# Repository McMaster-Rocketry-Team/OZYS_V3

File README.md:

# OZYS_PCB
OZYS PCB and Schematics

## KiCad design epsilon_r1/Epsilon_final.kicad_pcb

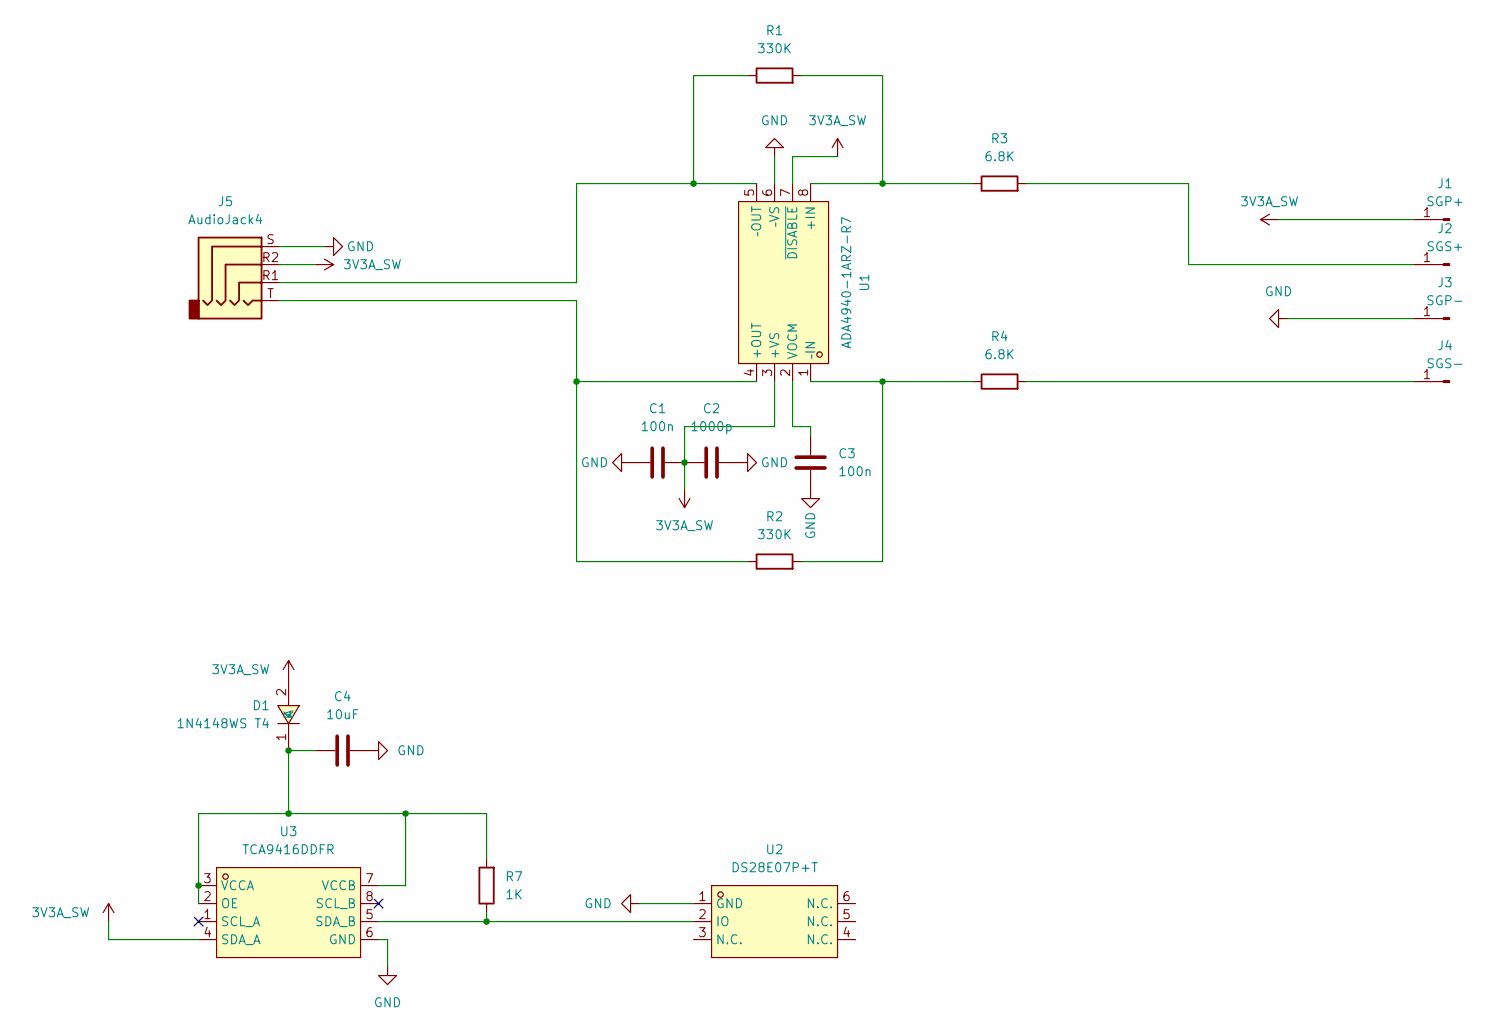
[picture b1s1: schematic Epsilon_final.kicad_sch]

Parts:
C1, C3: 100n; C_0402_1005Metric
C2: 1000p; C_0402_1005Metric
C4: 10uF; C_0402_1005Metric
D1: 1N4148WS T4; SOD-323_L1.8-W1.3-LS2.5-RD; LCSC Part C2128
J1: SGP+; SolderWirePad_1x01_SMD_1x2mm
J2: SGS+; SolderWirePad_1x01_SMD_1x2mm
J3: SGP-; SolderWirePad_1x01_SMD_1x2mm
J4: SGS-; SolderWirePad_1x01_SMD_1x2mm
J5: AudioJack4; AUDIO-TH_PJ-320A-4P-DIP
R1, R2: 330K; R_0603_1608Metric_Pad0.98x0.95mm_HandSolder
R3, R4: 6.8K; R_0603_1608Metric_Pad0.98x0.95mm_HandSolder
R7: 1K; R_0402_1005Metric
U1: ADA4940-1ARZ-R7; LFCSP-16_L3.0-W3.0-P0.50-BL-EP1.3; LCSC Part C730049
U2: DS28E07P+T; TSOC-6_L3.9-W4.3-P1.27-BL; LCSC Part C2063921
U3: TCA9416DDFR; TSOT-23-8_L2.9-W1.6-P0.65-LS2.8-BR; LCSC Part C4364143

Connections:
3V3A_SW: C1.1, C2.2, D1.2 (A), J1.1, J5.R2, U1.3 (+VS), U1.7 (~DISABLE), U3.4 (SDA_A)
GND: C1.2, C2.1, C3.1, C4.2, J3.1, J5.S, U1.6 (–VS), U2.1 (GND), U3.6 (GND)
unnamed: C4.1, D1.1 (K), R7.2, U3.2 (OE), U3.3 (VCCA), U3.7 (VCCB)
unnamed: J2.1, R3.2
unnamed: J4.1, R4.2
unnamed: R1.2, R3.1, U1.8 (+IN)
unnamed: J5.T, R2.1, U1.4 (+OUT)
unnamed: C3.2, U1.2 (VOCM)
unnamed: R2.2, R4.1, U1.1 (–IN)
unnamed: J5.R1, R1.1, U1.5 (–OUT)
unnamed: R7.1, U2.2 (IO), U3.5 (SDA_B)

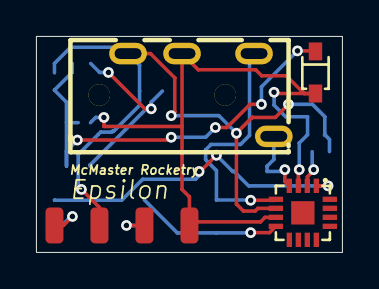
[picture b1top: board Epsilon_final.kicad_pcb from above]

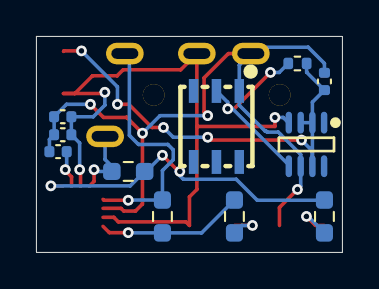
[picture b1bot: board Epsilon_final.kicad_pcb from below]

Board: 2 copper layers, 17.0 x 12.0 mm, 18 parts (11 on the bottom side), 11 nets.

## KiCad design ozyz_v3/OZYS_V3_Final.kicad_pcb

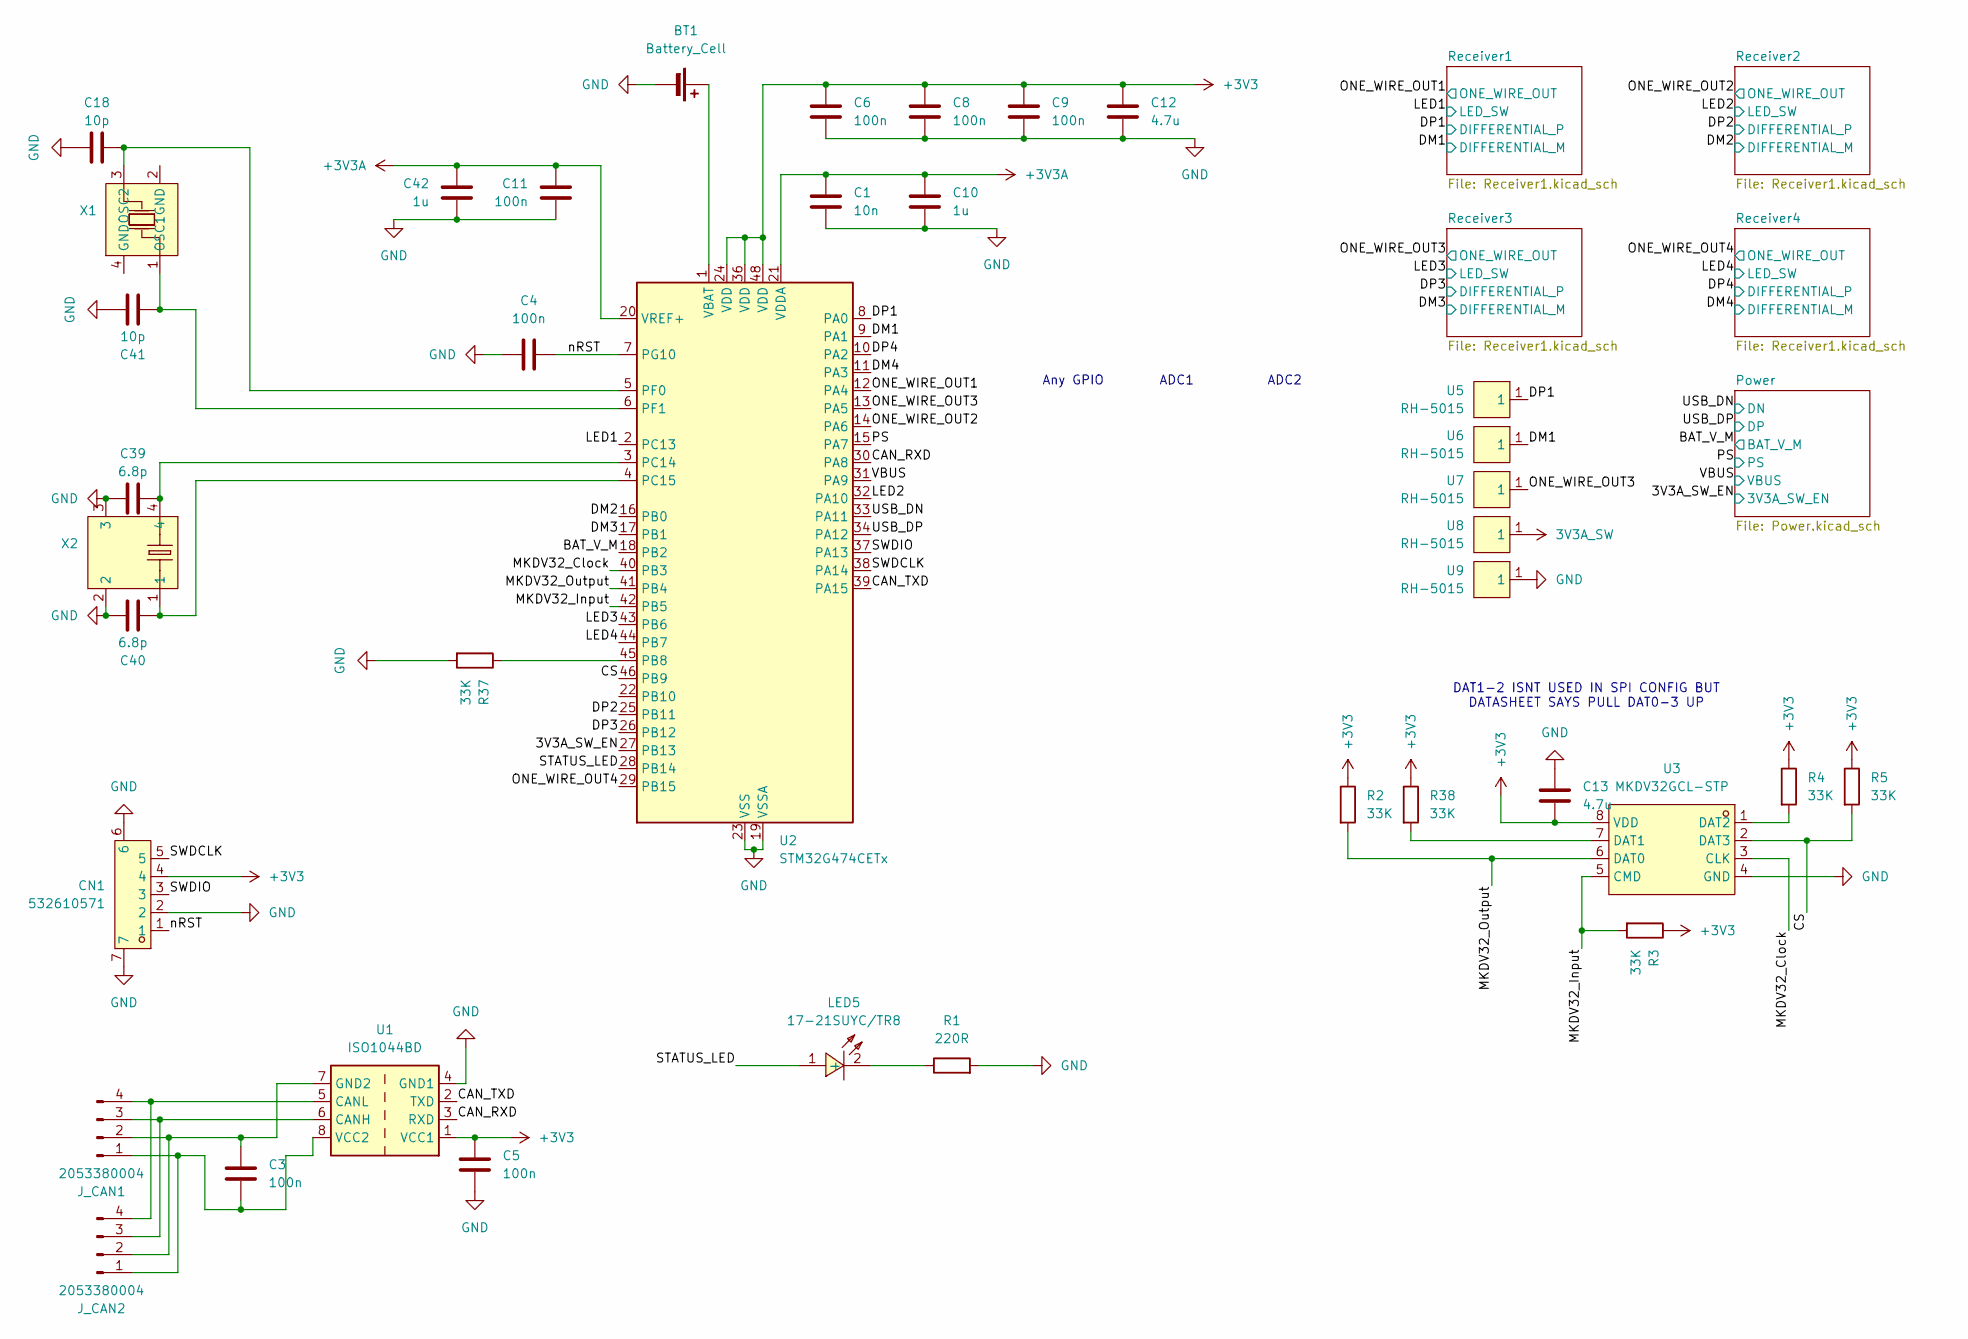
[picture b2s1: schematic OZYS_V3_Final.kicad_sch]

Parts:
BT1: Battery_Cell; SEIKO_ML414H_IV01E
C1: 10n; C_0402_1005Metric
C3, C4, C5, C6, C8, C9, C11: 100n; C_0402_1005Metric
C10, C42: 1u; C_0402_1005Metric
C12, C13: 4.7u; C_0402_1005Metric
C18, C41: 10p; C_0603_1608Metric_Pad1.08x0.95mm_HandSolder
C39, C40: 6.8p; C_0603_1608Metric_Pad1.08x0.95mm_HandSolder
CN1: 532610571; CONN-SMD_5P-P1.25_532610571-2; LCSC Part C392176
J_CAN1, J_CAN2: 2053380004; CONN_2053380000-SD_04_MOL
LED5: 17-21SUYC/TR8; LED0805-R-RD; LCSC Part C2296
R1: 220R; R_0402_1005Metric
R2, R3, R4, R5, R37, R38: 33K; R_0402_1005Metric
U1: ISO1044BD; SOIC-8_3.9x4.9mm_P1.27mm
U2: STM32G474CETx; LQFP-48_7x7mm_P0.5mm
U3: MKDV32GCL-STP; LGA-8_L6.0-W8.0-P1.27-TL; LCSC Part C7500179
U5, U6, U7, U8, U9: RH-5015; SMD_RH-5015; LCSC Part C5199798
X1: X322516MLB4SI; OSC-SMD_4P-L3.2-W2.5-BL; LCSC Part C13738
X2: MC-306 32.768kHz 6.0pF 20ppm; MC-306_4P-L8.0-W3.2-P5.5-BL; LCSC Part C83979

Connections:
3V3A_SW: U8.1; also elsewhere on the board
+3V3: C5.2, C6.1, C8.1, C9.1, C12.1, C13.2, CN1.4, R2.1, R3.1, R4.1, R5.1, R38.1, U1.1 (VCC1), U2.24 (VDD), U2.36 (VDD), U2.48 (VDD), U3.8 (VDD); also elsewhere on the board
+3V3A: C1.1, C10.2, C11.1, C42.2, U2.20 (VREF+), U2.21 (VDDA); also elsewhere on the board
/3V3A_SW_EN: U2.27 (PB13); also elsewhere on the board
/BAT_V_M: U2.18 (PB2); also elsewhere on the board
/CAN_RXD: U1.3 (RXD), U2.30 (PA8)
/CAN_TXD: U1.2 (TXD), U2.39 (PA15)
/CS: R5.2, U2.46 (PB9), U3.2 (DAT3)
/DM1: U2.9 (PA1), U6.1; also elsewhere on the board
/DM2: U2.16 (PB0); also elsewhere on the board
/DM3: U2.17 (PB1); also elsewhere on the board
/DM4: U2.11 (PA3); also elsewhere on the board
/DP1: U2.8 (PA0), U5.1; also elsewhere on the board
/DP2: U2.25 (PB11); also elsewhere on the board
/DP3: U2.26 (PB12); also elsewhere on the board
/DP4: U2.10 (PA2); also elsewhere on the board
/LED1: U2.2 (PC13); also elsewhere on the board
/LED2: U2.32 (PA10); also elsewhere on the board
/LED3: U2.43 (PB6); also elsewhere on the board
/LED4: U2.44 (PB7); also elsewhere on the board
/MKDV32_Clock: U2.40 (PB3), U3.3 (CLK)
/MKDV32_Input: R3.2, U2.42 (PB5), U3.5 (CMD)
/MKDV32_Output: R2.2, U2.41 (PB4), U3.6 (DAT0)
/ONE_WIRE_OUT1: U2.12 (PA4); also elsewhere on the board
/ONE_WIRE_OUT2: U2.14 (PA6); also elsewhere on the board
/ONE_WIRE_OUT3: U2.13 (PA5), U7.1; also elsewhere on the board
/ONE_WIRE_OUT4: U2.29 (PB15); also elsewhere on the board
/PS: U2.15 (PA7); also elsewhere on the board
/STATUS_LED: LED5.1 (+), U2.28 (PB14)
/SWDCLK: CN1.5, U2.38 (PA14)
/SWDIO: CN1.3, U2.37 (PA13)
/USB_DN: U2.33 (PA11); also elsewhere on the board
/USB_DP: U2.34 (PA12); also elsewhere on the board
/VBUS: U2.31 (PA9); also elsewhere on the board
/nRST: C4.2, CN1.1, U2.7 (PG10)
GND: BT1.2 (-), C1.2, C4.1, C5.1, C6.2, C8.2, C9.2, C10.1, C11.2, C12.2, C13.1, C18.1, C39.1, C40.2, C41.1, C42.1, CN1.2, CN1.6, CN1.7, R1.2, R37.2, U1.4 (GND1), U2.19 (VSSA), U2.23 (VSS), U2.35 (VSS), U2.47 (VSS), U3.4 (GND), U9.1, X2.2, X2.3; also elsewhere on the board
unnamed: BT1.1 (+), U2.1 (VBAT)
unnamed: C3.2, J_CAN1.1, J_CAN2.1, U1.8 (VCC2)
unnamed: C3.1, J_CAN1.2, J_CAN2.2, U1.7 (GND2)
unnamed: J_CAN1.3, J_CAN2.3, U1.6 (CANH)
unnamed: J_CAN1.4, J_CAN2.4, U1.5 (CANL)
unnamed: LED5.2 (-), R1.1
unnamed: R37.1, U2.45 (PB8)
unnamed: C39.2, U2.3 (PC14), X2.4
unnamed: C40.1, U2.4 (PC15), X2.1
unnamed: C18.2, U2.5 (PF0), X1.3 (OSC2)
unnamed: C41.2, U2.6 (PF1), X1.1 (OSC1)
unnamed: R38.2, U3.7 (DAT1)
unnamed: R4.2, U3.1 (DAT2)

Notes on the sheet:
ADC1
ADC2
DAT1-2 ISNT USED IN SPI CONFIG BUT DATASHEET SAYS PULL DAT0-3 UP
Any GPIO

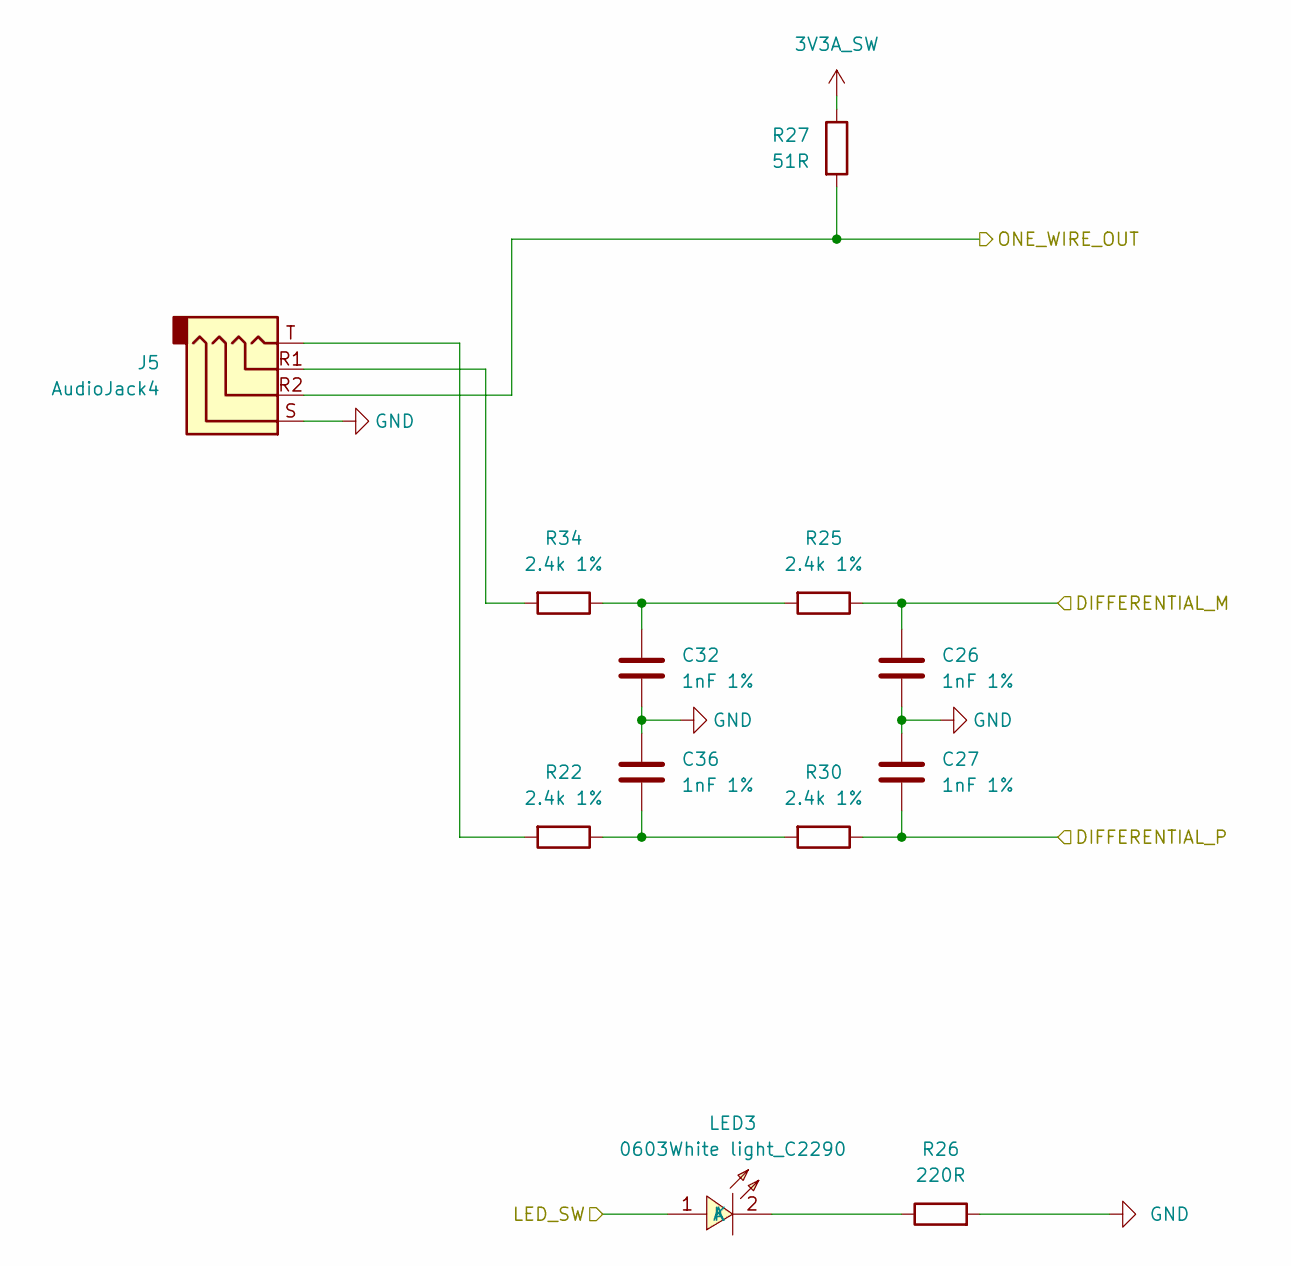
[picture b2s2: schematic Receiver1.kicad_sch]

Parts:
C26, C27, C32, C36: 1nF 1%; C_0603_1608Metric_Pad1.08x0.95mm_HandSolder
J5: AudioJack4; AUDIO-TH_PJ-320A-4P-DIP
LED3: 0603White light_C2290; LED0603-R-RD_WHITE; LCSC Part C2290
R22, R25, R30, R34: 2.4k 1%; C_0603_1608Metric_Pad1.08x0.95mm_HandSolder
R26: 220R; R_0402_1005Metric
R27: 51R; R_0402_1005Metric

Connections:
3V3A_SW: R27.1; also elsewhere on the board
/DM3: C26.1, R25.1; also elsewhere on the board
/DP3: C27.2, R30.1; also elsewhere on the board
/LED3: LED3.1 (A); also elsewhere on the board
/ONE_WIRE_OUT3: J5.R2, R27.2; also elsewhere on the board
GND: C26.2, C27.1, C32.2, C36.1, J5.S, R26.2; also elsewhere on the board
unnamed: C32.1, R25.2, R34.1
unnamed: C36.2, R22.1, R30.2
unnamed: J5.R1, R34.2
unnamed: J5.T, R22.2
unnamed: LED3.2 (K), R26.1

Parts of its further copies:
C2, C7, C22, C24, C28, C29, C30, C31, C33, C34, C35, C37: 1nF 1%; C_0603_1608Metric_Pad1.08x0.95mm_HandSolder
J3, J4, J6: AudioJack4; AUDIO-TH_PJ-320A-4P-DIP
LED1, LED2, LED4: 0603White light_C2290; LED0603-R-RD_WHITE; LCSC Part C2290
R13, R14, R19, R20, R21, R23, R24, R28, R29, R31, R35, R36: 2.4k 1%; C_0603_1608Metric_Pad1.08x0.95mm_HandSolder
R15, R17, R32: 220R; R_0402_1005Metric
R16, R18, R33: 51R; R_0402_1005Metric

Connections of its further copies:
3V3A_SW: R16.1, R18.1, R33.1; also elsewhere on the board
/DM1: C2.1, R13.1; also elsewhere on the board
/DM2: C22.1, R21.1; also elsewhere on the board
/DM4: C28.1, R31.1; also elsewhere on the board
/DP1: C7.2, R14.1; also elsewhere on the board
/DP2: C24.2, R24.1; also elsewhere on the board
/DP4: C29.2, R36.1; also elsewhere on the board
/LED1: LED2.1 (A); also elsewhere on the board
/LED2: LED1.1 (A); also elsewhere on the board
/LED4: LED4.1 (A); also elsewhere on the board
/ONE_WIRE_OUT1: J3.R2, R16.2; also elsewhere on the board
/ONE_WIRE_OUT2: J4.R2, R18.2; also elsewhere on the board
/ONE_WIRE_OUT4: J6.R2, R33.2; also elsewhere on the board
GND: C2.2, C7.1, C22.2, C24.1, C28.2, C29.1, C30.2, C31.2, C33.2, C34.1, C35.1, C37.1, J3.S, J4.S, J6.S, R15.2, R17.2, R32.2; also elsewhere on the board
unnamed: C30.1, R13.2, R28.1
unnamed: C31.1, R21.2, R29.1
unnamed: C33.1, R31.2, R35.1
unnamed: C34.2, R14.2, R19.1
unnamed: C35.2, R20.1, R24.2
unnamed: C37.2, R23.1, R36.2
unnamed: J3.R1, R28.2
unnamed: J3.T, R19.2
unnamed: J4.R1, R29.2
unnamed: J4.T, R20.2
unnamed: J6.R1, R35.2
unnamed: J6.T, R23.2
unnamed: LED1.2 (K), R17.1
unnamed: LED2.2 (K), R15.1
unnamed: LED4.2 (K), R32.1

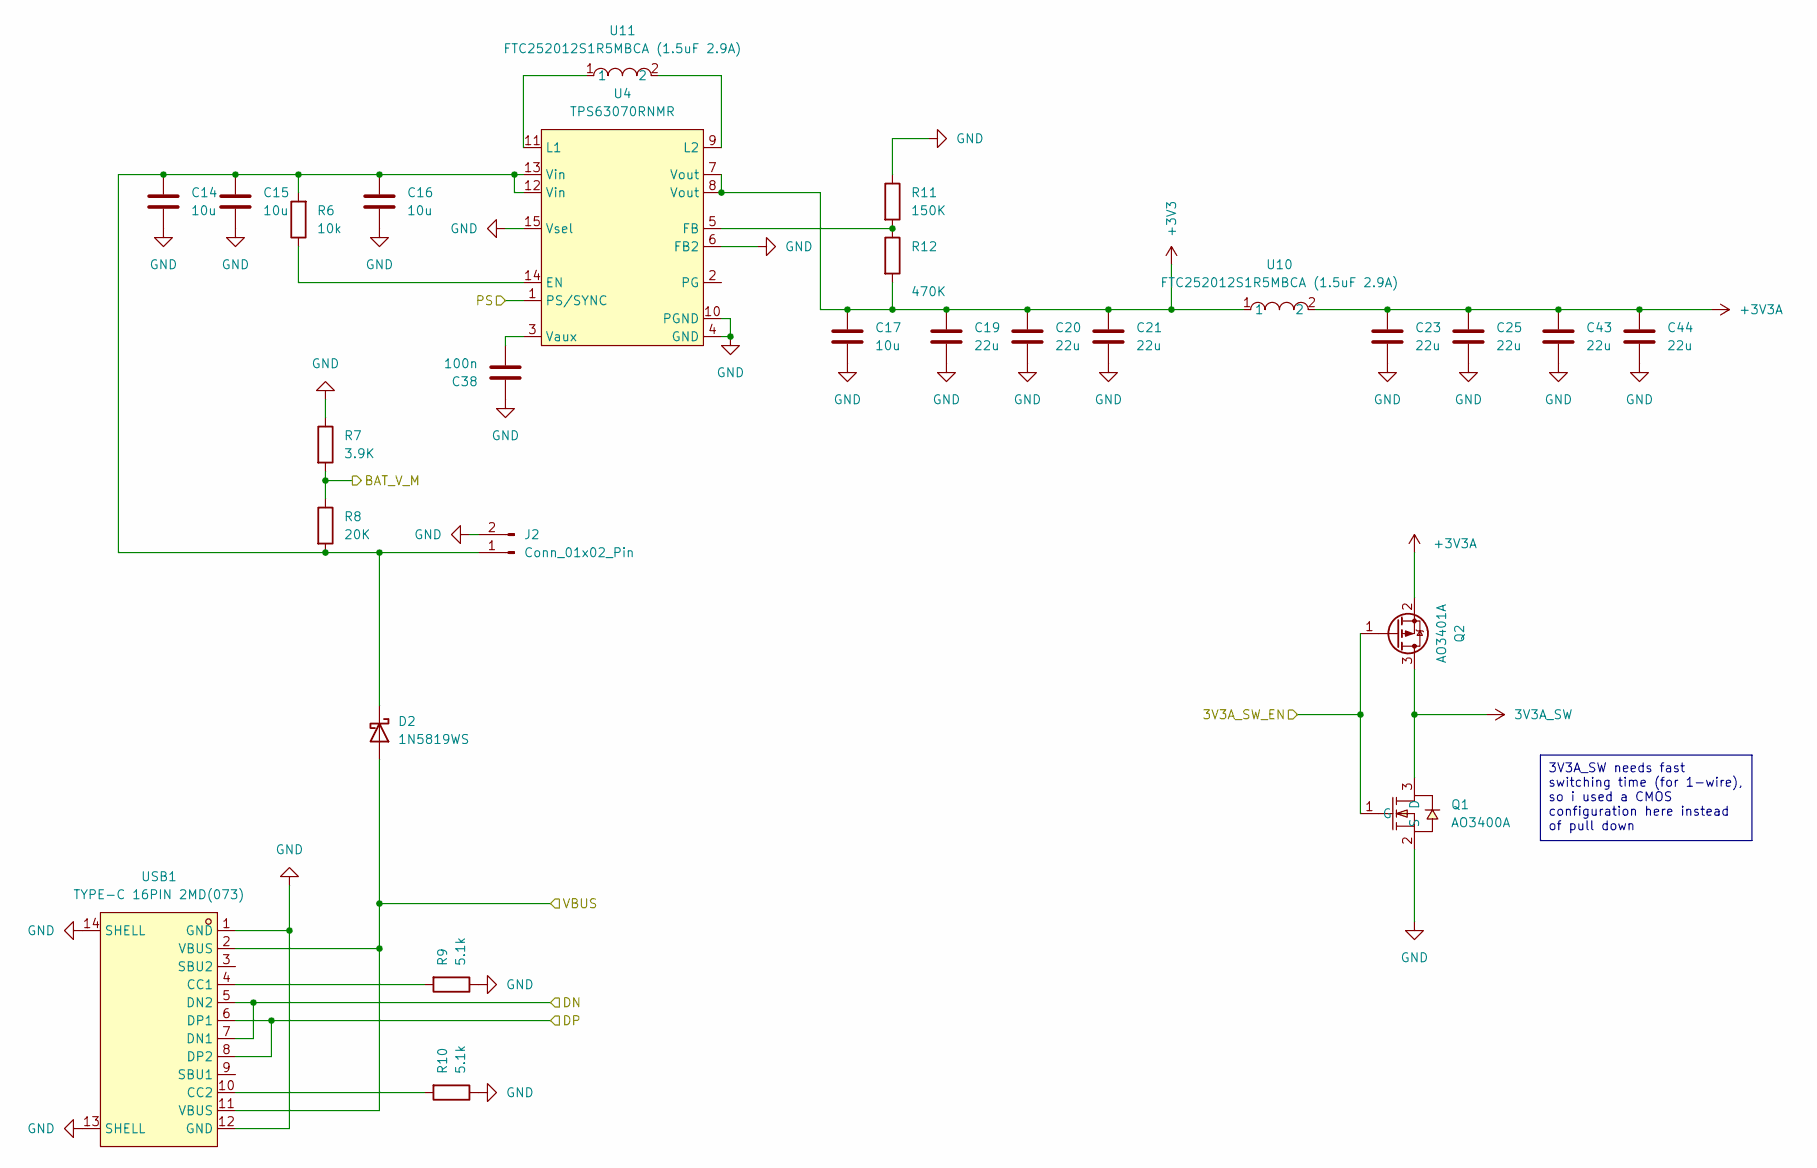
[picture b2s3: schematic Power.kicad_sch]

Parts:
C14, C15, C16, C17: 10u; C_0603_1608Metric
C19, C20, C21, C23, C25, C43, C44: 22u; C_0603_1608Metric
C38: 100n; C_0402_1005Metric
D2: 1N5819WS; D_SOD-323
J2: Conn_01x02_Pin; 1054301102
Q1: AO3400A; SOT-23-3_L2.9-W1.3-P1.90-LS2.4-BR; LCSC Part C20917
Q2: AO3401A; SOT-23
R6: 10k; R_0402_1005Metric
R7: 3.9K; R_0402_1005Metric
R8: 20K; R_0402_1005Metric
R9, R10: 5.1k; R_0402_1005Metric
R11: 150K; R_0402_1005Metric
R12: 470K; R_0402_1005Metric
U4: TPS63070RNMR; VQFN-HR-15_L3.0-W2.5-P0.50-BL_TPS63070RNMR; LCSC Part C109322
U10, U11: FTC252012S1R5MBCA (1.5uF 2.9A); IND-SMD_L2.5-W2.0_MEKK2520TR47M; LCSC Part C5832371
USB1: TYPE-C 16PIN 2MD(073); USB-C-SMD_TYPE-C-6PIN-2MD-073; LCSC Part C2765186

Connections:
3V3A_SW: Q1.3 (D), Q2.3 (D); also elsewhere on the board
+3V3: C17.2, C19.2, C20.2, C21.2, R12.2, U4.7 (Vout), U4.8 (Vout), U10.1; also elsewhere on the board
+3V3A: C23.2, C25.2, C43.2, C44.2, Q2.2 (S), U10.2; also elsewhere on the board
/3V3A_SW_EN: Q1.1 (G), Q2.1 (G); also elsewhere on the board
/BAT_V_M: R7.2, R8.1; also elsewhere on the board
/PS: U4.1 (PS/SYNC); also elsewhere on the board
/USB_DN: USB1.5 (DN2), USB1.7 (DN1); also elsewhere on the board
/USB_DP: USB1.6 (DP1), USB1.8 (DP2); also elsewhere on the board
/VBUS: D2.2 (A), USB1.2 (VBUS), USB1.11 (VBUS); also elsewhere on the board
GND: C14.1, C15.1, C16.1, C17.1, C19.1, C20.1, C21.1, C23.1, C25.1, C38.2, C43.1, C44.1, J2.2, Q1.2 (S), R7.1, R9.1, R10.1, R11.1, U4.4 (GND), U4.6 (FB2), U4.10 (PGND), U4.15 (Vsel), USB1.1 (GND), USB1.12 (GND), USB1.13 (SHELL), USB1.14 (SHELL); also elsewhere on the board
unnamed: C14.2, C15.2, C16.2, D2.1 (K), J2.1, R6.2, R8.2, U4.12 (Vin), U4.13 (Vin)
unnamed: R6.1, U4.14 (EN)
unnamed: R11.2, R12.1, U4.5 (FB)
unnamed: U4.11 (L1), U11.1
unnamed: U4.9 (L2), U11.2
unnamed: C38.1, U4.3 (Vaux)
unnamed: R9.2, USB1.4 (CC1)
unnamed: R10.2, USB1.10 (CC2)

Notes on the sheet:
3V3A_SW needs fast switching time (for 1-wire), so i used a CMOS configuration here instead of pull down

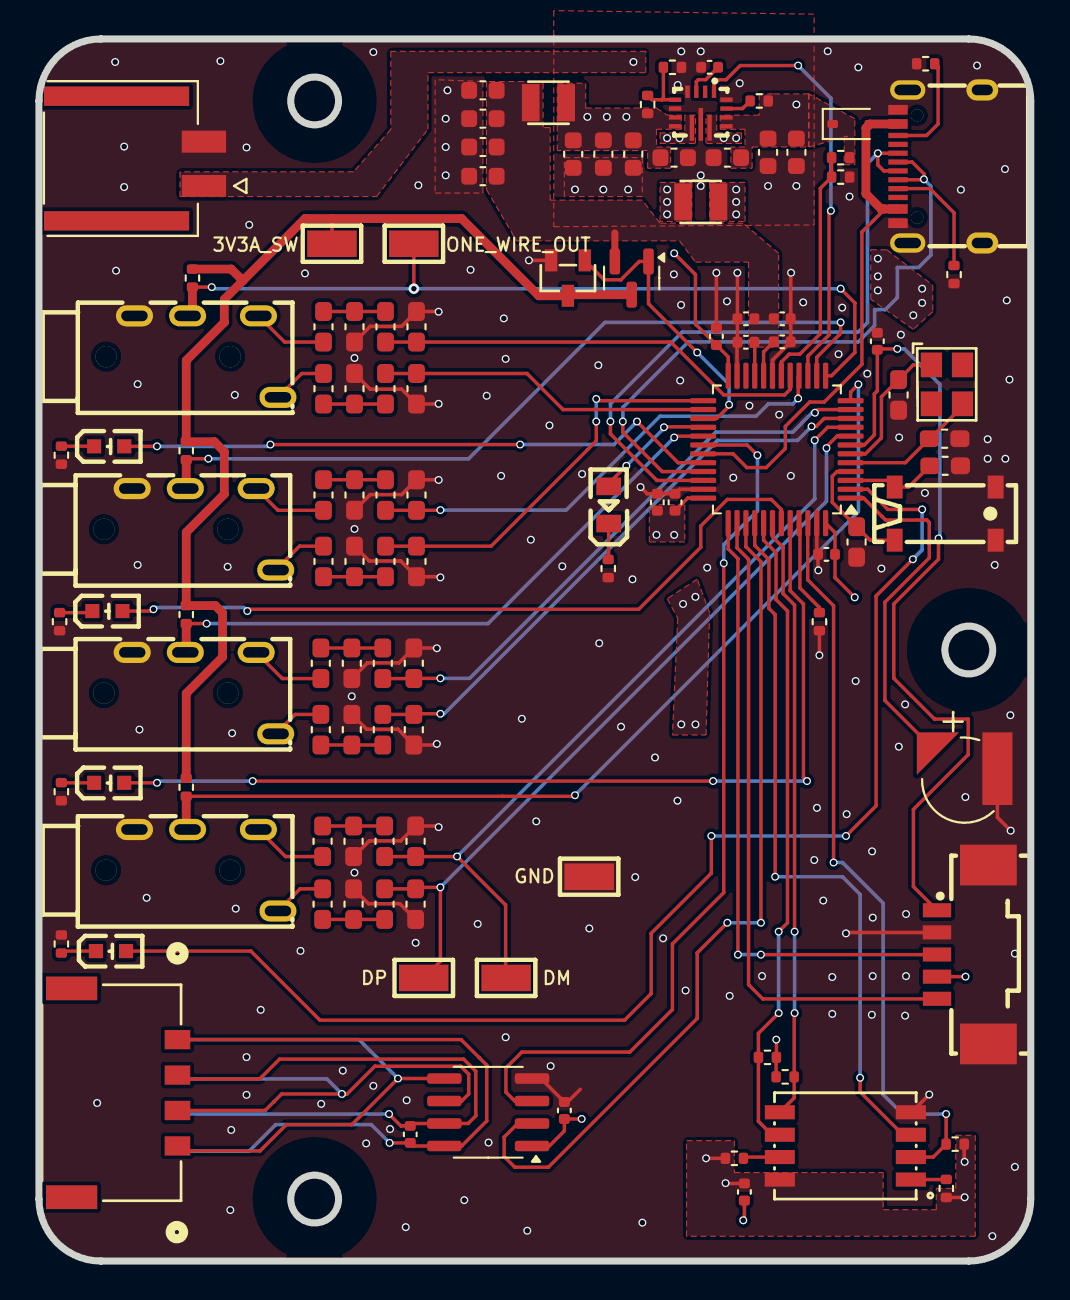
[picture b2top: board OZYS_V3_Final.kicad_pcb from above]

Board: 4 copper layers, 56.0 x 69.0 mm, 113 parts (1 on the bottom side), 77 nets.

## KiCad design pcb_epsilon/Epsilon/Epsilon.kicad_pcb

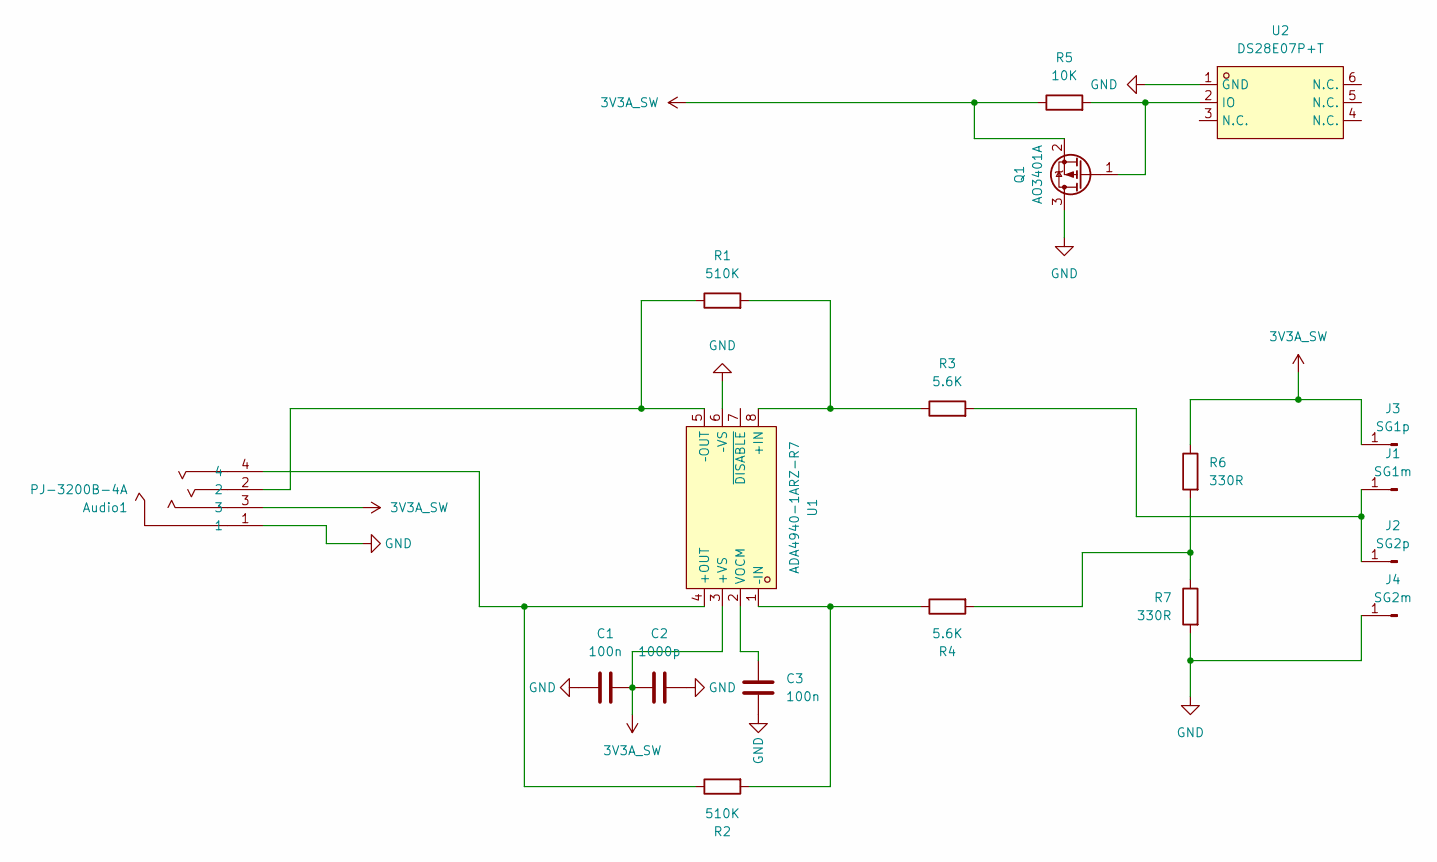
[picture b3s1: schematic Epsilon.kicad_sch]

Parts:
Audio1: PJ-3200B-4A; AUDIO-TH_PJ-3200B-4A; LCSC Part C136687
C1, C3: 100n; C_0402_1005Metric
C2: 1000p; C_0402_1005Metric
J1: SG1m; SolderWirePad_1x01_SMD_1x2mm
J2: SG2p; SolderWirePad_1x01_SMD_1x2mm
J3: SG1p; SolderWirePad_1x01_SMD_1x2mm
J4: SG2m; SolderWirePad_1x01_SMD_1x2mm
Q1: AO3401A; SOT-23
R1, R2: 510K; R_0603_1608Metric_Pad0.98x0.95mm_HandSolder
R3, R4: 5.6K; R_0603_1608Metric_Pad0.98x0.95mm_HandSolder
R5: 10K; R_0402_1005Metric_Pad0.72x0.64mm_HandSolder
R6, R7: 330R; R_0402_1005Metric_Pad0.72x0.64mm_HandSolder
U1: ADA4940-1ARZ-R7; SOIC-8_L4.9-W3.9-P1.27-LS6.0-BL; LCSC Part C730049
U2: DS28E07P+T; TSOC-6_L3.9-W4.3-P1.27-BL; LCSC Part C2063921

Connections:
3V3A_SW: Audio1.3, C1.1, C2.2, J3.1, Q1.2 (S), R5.1, R6.1, U1.3 (+VS)
GND: Audio1.1, C1.2, C2.1, C3.1, J4.1, Q1.3 (D), R7.2, U1.6 (–VS), U2.1 (GND)
unnamed: J1.1, J2.1, R3.2
unnamed: Q1.1 (G), R5.2, U2.2 (IO)
unnamed: R4.2, R6.2, R7.1
unnamed: R1.2, R3.1, U1.8 (+IN)
unnamed: Audio1.4, R2.1, U1.4 (+OUT)
unnamed: C3.2, U1.2 (VOCM)
unnamed: R2.2, R4.1, U1.1 (–IN)
unnamed: Audio1.2, R1.1, U1.5 (–OUT)

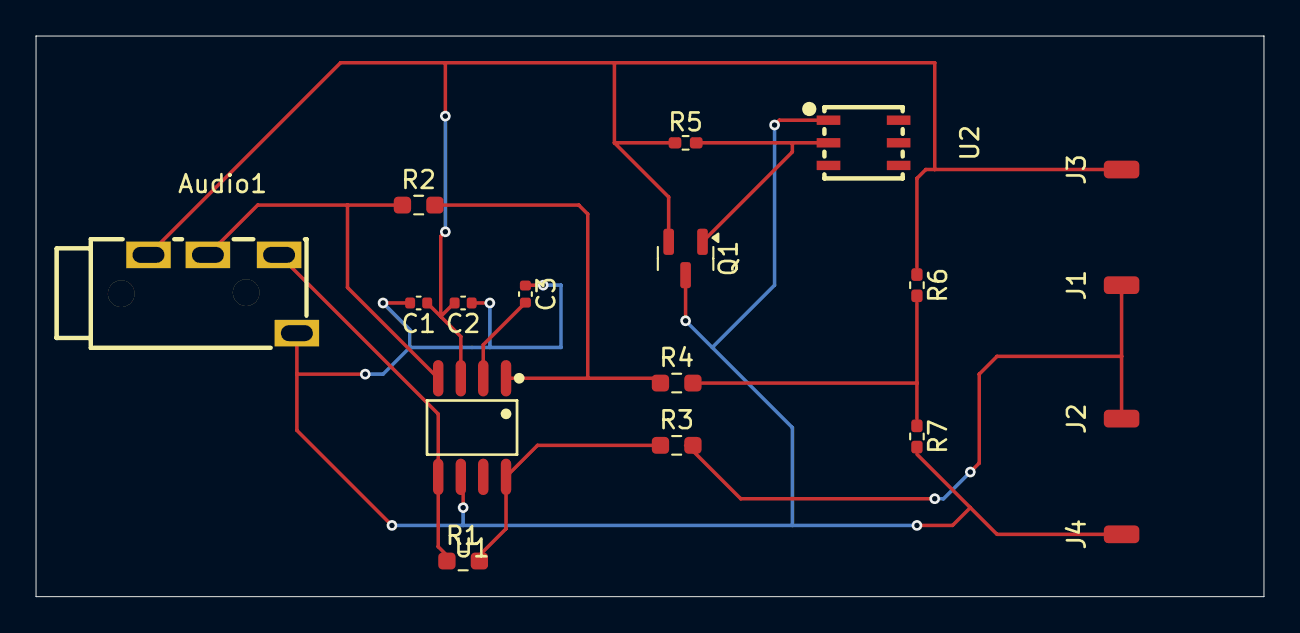
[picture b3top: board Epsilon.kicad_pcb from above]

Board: 2 copper layers, 69.0 x 31.5 mm, 18 parts (0 on the bottom side), 10 nets.

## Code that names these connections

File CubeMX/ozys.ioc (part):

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Mcu.Name=STM32G474C(B-C-E)Tx
Mcu.Package=LQFP48
Mcu.UserName=STM32G474CETx
PA0.Mode=IN1-Differential
PA0.Signal=ADC1_IN1
PA1.Mode=IN1-Differential
PA1.Signal=ADC1_IN2
PA11.Mode=Device
PA11.Signal=USB_DM
PA12.Mode=Device
PA12.Signal=USB_DP
PA13.Mode=Serial_Wire
PA13.Signal=SYS_JTMS-SWDIO
PA14.Mode=Serial_Wire
PA14.Signal=SYS_JTCK-SWCLK
PA15.Mode=FDCAN_Activate
PA15.Signal=FDCAN3_TX
PA2.Mode=IN3-Differential
PA2.Signal=ADC1_IN3
PA3.Mode=IN3-Differential
PA3.Signal=ADC1_IN4
PA4.Mode=IN17-Single-Ended
PA4.Signal=ADC2_IN17
PA5.Mode=IN13-Single-Ended
PA5.Signal=ADC2_IN13
PA6.Mode=IN3-Single-Ended
PA6.Signal=ADC2_IN3
PA8.Mode=FDCAN_Activate
PA8.Signal=FDCAN3_RX
PB0.Mode=IN14-Differential
PB0.Signal=ADC1_IN15
PB1.Mode=IN11-Differential
PB1.Signal=ADC1_IN12
PB11.Mode=IN14-Differential
PB11.Signal=ADC1_IN14
PB12.Mode=IN11-Differential
PB12.Signal=ADC1_IN11
PB15.Mode=IN15-Single-Ended
PB15.Signal=ADC2_IN15
PB2.Mode=IN12-Single-Ended
PB2.Signal=ADC2_IN12
PB3.Mode=Full_Duplex_Master
PB3.Signal=SPI1_SCK
PB4.Mode=Full_Duplex_Master
PB4.Signal=SPI1_MISO
PB5.Mode=Full_Duplex_Master
PB5.Signal=SPI1_MOSI
PC14-OSC32_IN.Mode=LSE-External-Oscillator
PC14-OSC32_IN.Signal=RCC_OSC32_IN
PC15-OSC32_OUT.Mode=LSE-External-Oscillator
PC15-OSC32_OUT.Signal=RCC_OSC32_OUT
PF0-OSC_IN.Mode=HSE-External-Oscillator
PF0-OSC_IN.Signal=RCC_OSC_IN
PF1-OSC_OUT.Mode=HSE-External-Oscillator
PF1-OSC_OUT.Signal=RCC_OSC_OUT
RCC.HSE_VALUE=16000000
RCC.SYSCLKFreq_VALUE=150000000
RCC.SYSCLKSource=RCC_SYSCLKSOURCE_PLLCLK
board=custom

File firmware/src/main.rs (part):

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    Peri,
    adc::{Adc, AdcChannel, SampleTime},
    crc::{Config as CrcConfig, Crc, InputReverseConfig, PolySize},
    peripherals::{ADC1, DMA1_CH1, PA0, PA2, PA10, PB6, PB7, PB11, PB12, PB14, PC13},
};
use embassy_stm32::{
    gpio::{Level, Output, Speed},
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
use embassy_embedded_hal::shared_bus::asynch::spi::SpiDevice;
use embassy_stm32::spi::{Config as SpiConfig, Spi};
use embassy_stm32::{peripherals::PB3, time::Hertz};
use embedded_sdmmc::asynchronous::{Block, BlockDevice as _, BlockIdx, SdCard};
use firmware_common_new::can_bus::{
    custom_status::ozys_custom_status::OzysCustomStatus,
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    // Peripherals

    // TOP TO BOTTOM ORDERING OF LEDS
    // led 2: PA10
    // led 3: PB6
    // led 4: PB7
    // led 1: PC13
    // status led: PB14

    let ps = Output::new(p.PA7, Level::Low, Speed::Low); // PS pin, low: force pwm 
    mem::forget(ps);

    let (can_sender, can_receiver) = start_can_bus_tasks(&spawner, p.FDCAN3, p.PA8, p.PA15).await;
    spawner.must_spawn(watchdog_task(p.IWDG));
    spawner.must_spawn(node_status_task(can_sender));
    spawner.must_spawn(status_led_task(p.PB14));
    spawner.must_spawn(can_vl_status_check(
        can_receiver,
        flight_stage_watch.sender(),
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    spawner.must_spawn(adc_test_task(
        adc,
        p.DMA1_CH1,
        p.PA0,
        p.PA2,
        p.PB11,
        p.PB12,
        read_buffer,
        adc_samples_channel.publisher().unwrap(),
        converted_samples,
        flight_stage_watch.receiver().unwrap(),
        p.PA10,
        p.PB6,
        p.PB7,
        p.PC13,
    ));

    // sd
    let cs = Output::new(p.PB9, Level::High, Speed::High); // needed to configure as spi mode on peripheral  
    let mut spi_config = SpiConfig::default();
    spi_config.frequency = Hertz(5_000_000);
    let spi1: Spi<'static, embassy_stm32::mode::Async> = Spi::new(
        p.SPI1, p.PB3, p.PB5, p.PB4, p.DMA1_CH2, p.DMA1_CH3, spi_config,
    );
    let spi1 = singleton!(:Mutex<NoopRawMutex, Spi<'static, embassy_stm32::mode::Async>> = Mutex::new(spi1)).unwrap();
    let crc_config =
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async fn adc_test_task(
    mut adc_peripheral: Adc<'static, ADC1>,
    mut dma_chanel: Peri<'static, DMA1_CH1>,
    mut adc_pin_1: Peri<'static, PA0>,
    mut adc_pin_2: Peri<'static, PA2>,
    mut adc_pin_3: Peri<'static, PB11>,
    mut adc_pin_4: Peri<'static, PB12>,
    read_buffer: &'static mut [u16; 5],
    publisher: Publisher<'static, NoopRawMutex, [f32; 4], 620, 2, 1>,
    converted_samples: &'static mut [f32; 4],
    mut state_watch_rx: embassy_sync::watch::Receiver<'static, NoopRawMutex, FlightStage, 2>,
    led_2_pin: Peri<'static, PA10>,
    led_3_pin: Peri<'static, PB6>,
    led_4_pin: Peri<'static, PB7>,
    led_1_pin: Peri<'static, PC13>,
) {
    let mut vrefint_channel = adc_peripheral.enable_vrefint().degrade_adc();
    adc_peripheral.set_sample_time(SampleTime::CYCLES247_5);
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    adc_peripheral.set_differential(&mut adc_pin_2, true);
    adc_peripheral.set_differential(&mut adc_pin_3, true);
    adc_peripheral.set_differential(&mut adc_pin_4, true);
    let mut pa0 = adc_pin_1.degrade_adc();
    let mut pa2 = adc_pin_2.degrade_adc();
    let mut pb11 = adc_pin_3.degrade_adc();
    let mut pb12 = adc_pin_4.degrade_adc();
    let VREFINT_CAL = 0x1FFF75AA as *mut u16;
    let vref_cal = unsafe { ptr::read_volatile(VREFINT_CAL) as f32 };
    info!("VREFINT_CAL: {}", vref_cal);
    let mut ticker = Ticker::every(Duration::from_hz(22_000));
    let mut _led2 = Output::new(led_2_pin, Level::Low, Speed::Low); // good 
    let mut _led3 = Output::new(led_3_pin, Level::Low, Speed::Low); // good
    let mut _led4 = Output::new(led_4_pin, Level::Low, Speed::Low); // good 
    let mut _led1 = Output::new(led_1_pin, Level::Low, Speed::Low); // good

    let mut last_state = state_watch_rx.get().await;
    loop {
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                        | FlightStage::DrogueChute
                        | FlightStage::MainChute
                ) {
                    // led 2: PA10
                    // led 3: PB6
                    // led 4: PB7
                    // led 1: PC13
                    // status led: PB14
                    _led2.set_high();
                    _led3.set_high();
                    _led4.set_high();
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                            dma_chanel.reborrow(),
                            [
                                (&mut vrefint_channel, SampleTime::CYCLES12_5),
                                (&mut pa0, SampleTime::CYCLES12_5),
                                (&mut pa2, SampleTime::CYCLES12_5),
                                (&mut pb11, SampleTime::CYCLES12_5),
                                (&mut pb12, SampleTime::CYCLES12_5),
                            ]
                            .into_iter(),
                            read_buffer,
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}

#[embassy_executor::task]
async fn status_led_task(yellow_led: Peri<'static, PB14>) {
    let mut yellow_led = Output::new(yellow_led, Level::High, Speed::Low);
    let mut ticker = Ticker::every(Duration::from_millis(1000));
    loop {
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
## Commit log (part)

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2024-11-08 Init Ozys Simulink
2024-11-10 Init Ozys Receiver simscape model
2024-11-11 Updated Receiver Model testing functionality
2024-11-11 Modified transconductance stages
2024-11-17 Updated Receiver, Driver, and Strain Gauges.
    ~200x gain for driver
2024-11-18 change diff line driver model
2024-11-18 small changes
2024-11-29 Init Repo and uploading schematics
2024-11-29 renames and cleanup
2024-12-05 Started PCBs fixed connectors
    - Fixed Bypass on CAN
    - Seperated SG connectors from 2x1 to 1x1
    - Rough Draft of Epsilon
2024-12-10 Updated Epsilon PCB and Ozys Sch
2025-02-02 Yolo
    Nothing could go wrong
2025-02-02 Yolo2
    new Ozys
2025-02-03 OZYS and EPSILON schematics updated.
    OZYS
    - New 3.5 PJ-320A-4P DIP
    - Fixed TPS Regulator Connections
    - Fixed STM32 Connections
    - Added Associated .ioc for stm32 pin config
    - Loading Capacitance of LSE based off an5093 STM datasheet
2025-02-03 Updated simulink
    - New SG
    - New Gains
2025-02-07 epsilon ready for layout
2025-02-07 OZYS ready for layout
2025-02-07 remove simulink temp files
2025-02-07 update connector placement
2025-02-16 Epsilon PCB Finished
    Updated OZYS still WIP.
2025-02-16 add epsilon manufacturing files
2025-02-28 Saving Rough Iteration of Ozys V3
    -STM Pins to be configured with current layout
2025-02-28 Saving another rough trace
    saving for iteration purposes
2025-02-28 Fixed LEDs
    - Just need to clean it up then add pours and GND vias
2025-02-28 fixed connections and playing with pours
    as summary describes
2025-03-01 Test Config
    Testing config :)
2025-03-01 Got rid of LED Fet
    - restructuring
2025-03-01 Updated with Pours
    Only missing gnd pours on top and bottom copper planes
2025-03-02 small changes
    small changes
2025-03-02 Ozys finalized?
    Hopefully
2025-03-06 Pours fixed, no Graphics
    Made sure all pours conform to 8mils clearance and width, with Solid connections.
2025-03-06 Added Graphics in folder for Convenience
2025-03-06 final touches
2025-03-06 Graphics Added on back
    Yipiee
2025-03-06 Updated edge alignment and text
    Yipeee
2025-03-26 firmware
2025-05-02 ozys testing
2025-05-02 clock config
2025-05-02 sd test
2025-05-02 adc test
2025-05-02 fix led
2025-05-03 update cubeide file
2025-05-13 can test code
2025-05-13 can and ota
2025-05-13 boot loader
2025-05-13 bootloader wip
2025-05-15 bootloader working
2025-05-16 fix ota
2025-05-16 new bootloader
2025-05-16 working bootloader
2025-05-16 remove embassy boot dependency
2025-05-17 bootloader changes
2025-05-17 verify firmware
2025-05-17 bug fix
2025-05-17 update rust edition
2025-05-17 add readme
2025-05-17 update ota code
2025-05-17 small fixes
2025-05-22 fix warning
2025-05-25 Epsilon Symbol Fixed
    Epsilon Symbol Fixed
2025-05-26 epsilon_r2
2025-05-26 epsilon_r1
2025-05-30 fix build
2025-06-26 nightly executor
2025-07-11 add toggle pwm
2025-07-17 base64 public key
2025-07-28 improve bootloader
2025-07-29 update git ignore
2025-07-30 misc
2025-07-30 add pcb version to readme
2025-07-30 add rw to backup ram
2025-07-30 improve size.py
2025-07-30 mention rocket-cli in readme
2025-07-30 small refactoring
2025-07-31 disable-blocking-mode
2025-08-01 comments
2025-08-01 fix build; revert to probe-rs
2025-08-04 fix memory.x
2025-08-13 Working Basic Tests
2025-08-13 Basic Block Formatting test
2025-08-13 Write ADC to whole block test
2025-08-13 Write Single Block to SDCard
2025-08-13 Write Multi Blocks to SD
2025-08-16 f32 for sdwrite
2025-08-16 included checksum
2025-08-17 Fixed CRC
2025-08-17 Cooking or Cooked?
2025-08-17 save index in sdcard
2025-08-17 works
2025-08-18 yippee
2025-08-18 nice
2025-08-18 increased capacity and fixed leds
2025-08-18 cargo fix
2025-08-18 increase can tx buffer
2025-08-18 reset sd card on can reset task
